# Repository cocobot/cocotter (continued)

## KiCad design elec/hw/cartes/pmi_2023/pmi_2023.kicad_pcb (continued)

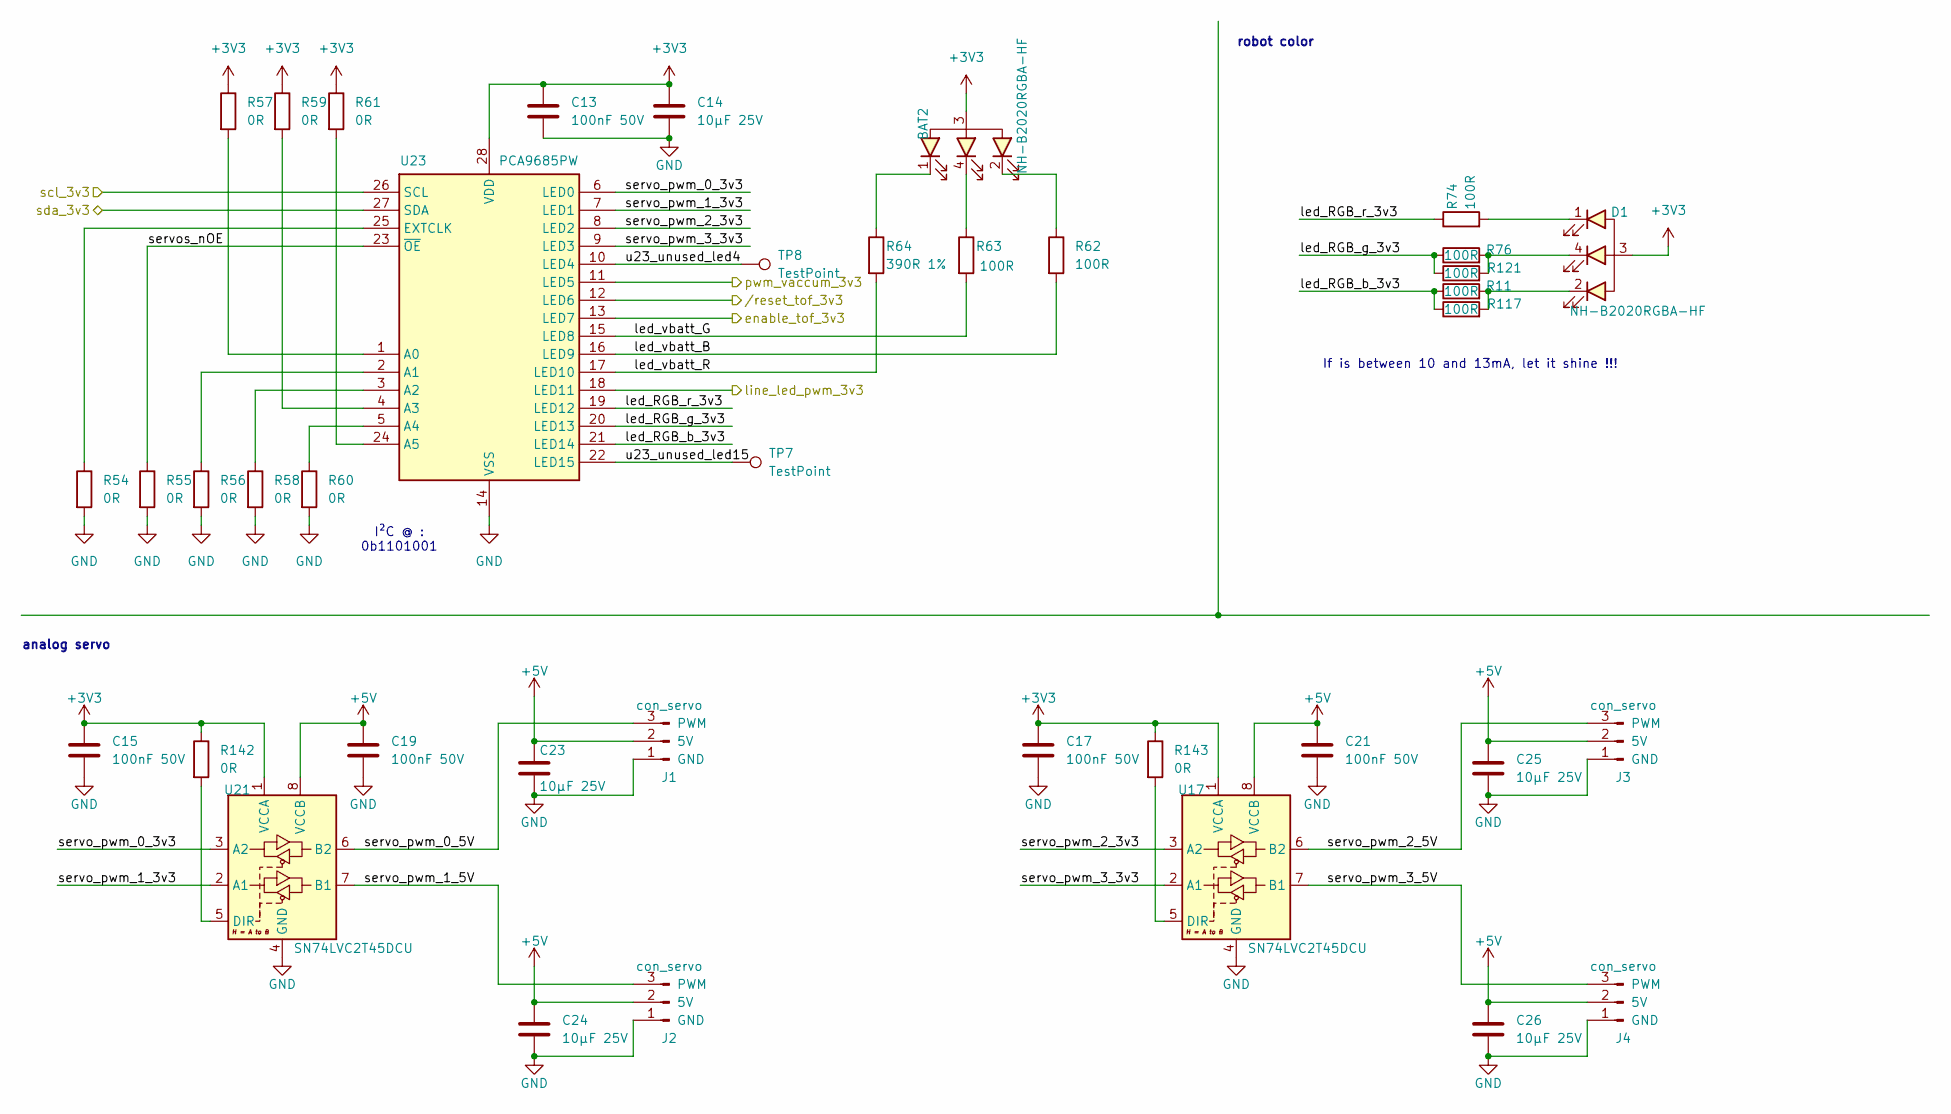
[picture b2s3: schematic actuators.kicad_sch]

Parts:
BAT2: NH-B2020RGBA-HF; JLCPCB Part # C2874116
C13, C15, C17, C19, C21: 100nF 50V; C_0603_1608Metric; JLCPCB Part # C14663
C14, C23, C24, C25, C26: 10µF 25V; C_0805_2012Metric; JLCPCB Part # C15850
D1: NH-B2020RGBA-HF; JLCPCB Part # C2874116
J1, J2, J3, J4: con_servo; ana_servo_5V; JLCPCB Part # C2932698
R11, R74, R76, R117, R121: 100R; r0603_reflow; JLCPCB Part # C22775
R54, R55, R56, R57, R58, R59, R60, R61, R142, R143: 0R; r0603_reflow; JLCPCB Part # C431718
R62, R63: 100R; r0603_reflow; mouser 603-RC0603FR-10100KL
R64: 390R 1%; r0603_reflow; mouser 603-RC0603FR-10100KL
TP7, TP8: TestPoint; testpoint-THT-0.5mm
U17, U21: SN74LVC2T45DCU; VSSOP-8-DCU
U23: PCA9685PW; TSSOP-28_4.4x9.7mm_P0.65mm; JLCPCB Part # C2678753

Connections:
+3V3: BAT2.3 (COM), C13.1, C14.1, C15.1, C17.1, D1.3 (COM), R57.1, R59.1, R61.1, R142.1, R143.1, U17.1 (VCCA), U21.1 (VCCA), U23.28 (VDD); also elsewhere on the board
+5V: C19.1, C21.1, C23.1, C24.1, C25.1, C26.1, J1.2 (5V), J2.2 (5V), J3.2 (5V), J4.2 (5V), U17.8 (VCCB), U21.8 (VCCB); also elsewhere on the board
/actuators/enable_tof_3v3: U23.13 (LED7); also elsewhere on the board
/actuators/led_RGB_b_3v3: R11.1, R117.1, U23.21 (LED14)
/actuators/led_RGB_g_3v3: R76.1, R121.1, U23.20 (LED13)
/actuators/led_RGB_r_3v3: R74.1, U23.19 (LED12)
/actuators/led_vbatt_B: R62.2, U23.16 (LED9)
/actuators/led_vbatt_G: R63.2, U23.15 (LED8)
/actuators/led_vbatt_R: R64.2, U23.17 (LED10)
/actuators/line_led_pwm_3v3: U23.18 (LED11); also elsewhere on the board
/actuators/scl_3v3: U23.26 (SCL); also elsewhere on the board
/actuators/sda_3v3: U23.27 (SDA); also elsewhere on the board
/actuators/servo_pwm_0_3v3: U21.3 (A2), U23.6 (LED0)
/actuators/servo_pwm_0_5V: J1.3 (PWM), U21.6 (B2)
/actuators/servo_pwm_1_3v3: U21.2 (A1), U23.7 (LED1)
/actuators/servo_pwm_1_5V: J2.3 (PWM), U21.7 (B1)
/actuators/servo_pwm_2_3v3: U17.3 (A2), U23.8 (LED2)
/actuators/servo_pwm_2_5V: J3.3 (PWM), U17.6 (B2)
/actuators/servo_pwm_3_3v3: U17.2 (A1), U23.9 (LED3)
/actuators/servo_pwm_3_5V: J4.3 (PWM), U17.7 (B1)
/actuators/servos_nOE: R55.1, U23.23 (~OE)
/actuators/u23_unused_led4: TP8.1, U23.10 (LED4)
/actuators/u23_unused_led15: TP7.1, U23.22 (LED15)
/actuators//reset_tof_3v3: U23.12 (LED6); also elsewhere on the board
/propulsion/pwm_vaccum_3v3: U23.11 (LED5); also elsewhere on the board
GND: C13.2, C14.2, C15.2, C17.2, C19.2, C21.2, C23.2, C24.2, C25.2, C26.2, J1.1 (GND), J2.1 (GND), J3.1 (GND), J4.1 (GND), R54.2, R55.2, R56.2, R58.2, R60.2, U17.4 (GND), U21.4 (GND), U23.14 (VSS); also elsewhere on the board
unnamed: BAT2.2 (C_BLUE), R62.1
unnamed: BAT2.4 (C_GREEN), R63.1
unnamed: BAT2.1 (C_RED), R64.1
unnamed: D1.2 (C_BLUE), R11.2, R117.2
unnamed: D1.4 (C_GREEN), R76.2, R121.2
unnamed: D1.1 (C_RED), R74.2
unnamed: R143.2, U17.5 (DIR)
unnamed: R142.2, U21.5 (DIR)
unnamed: R57.2, U23.1 (A0)
unnamed: R56.1, U23.2 (A1)
unnamed: R58.1, U23.3 (A2)
unnamed: R59.2, U23.4 (A3)
unnamed: R60.1, U23.5 (A4)
unnamed: R61.2, U23.24 (A5)
unnamed: R54.1, U23.25 (EXTCLK)

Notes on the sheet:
I²C @ : 0b1101001
If is between 10 and 13mA, let it shine !!!
robot color
analog servo

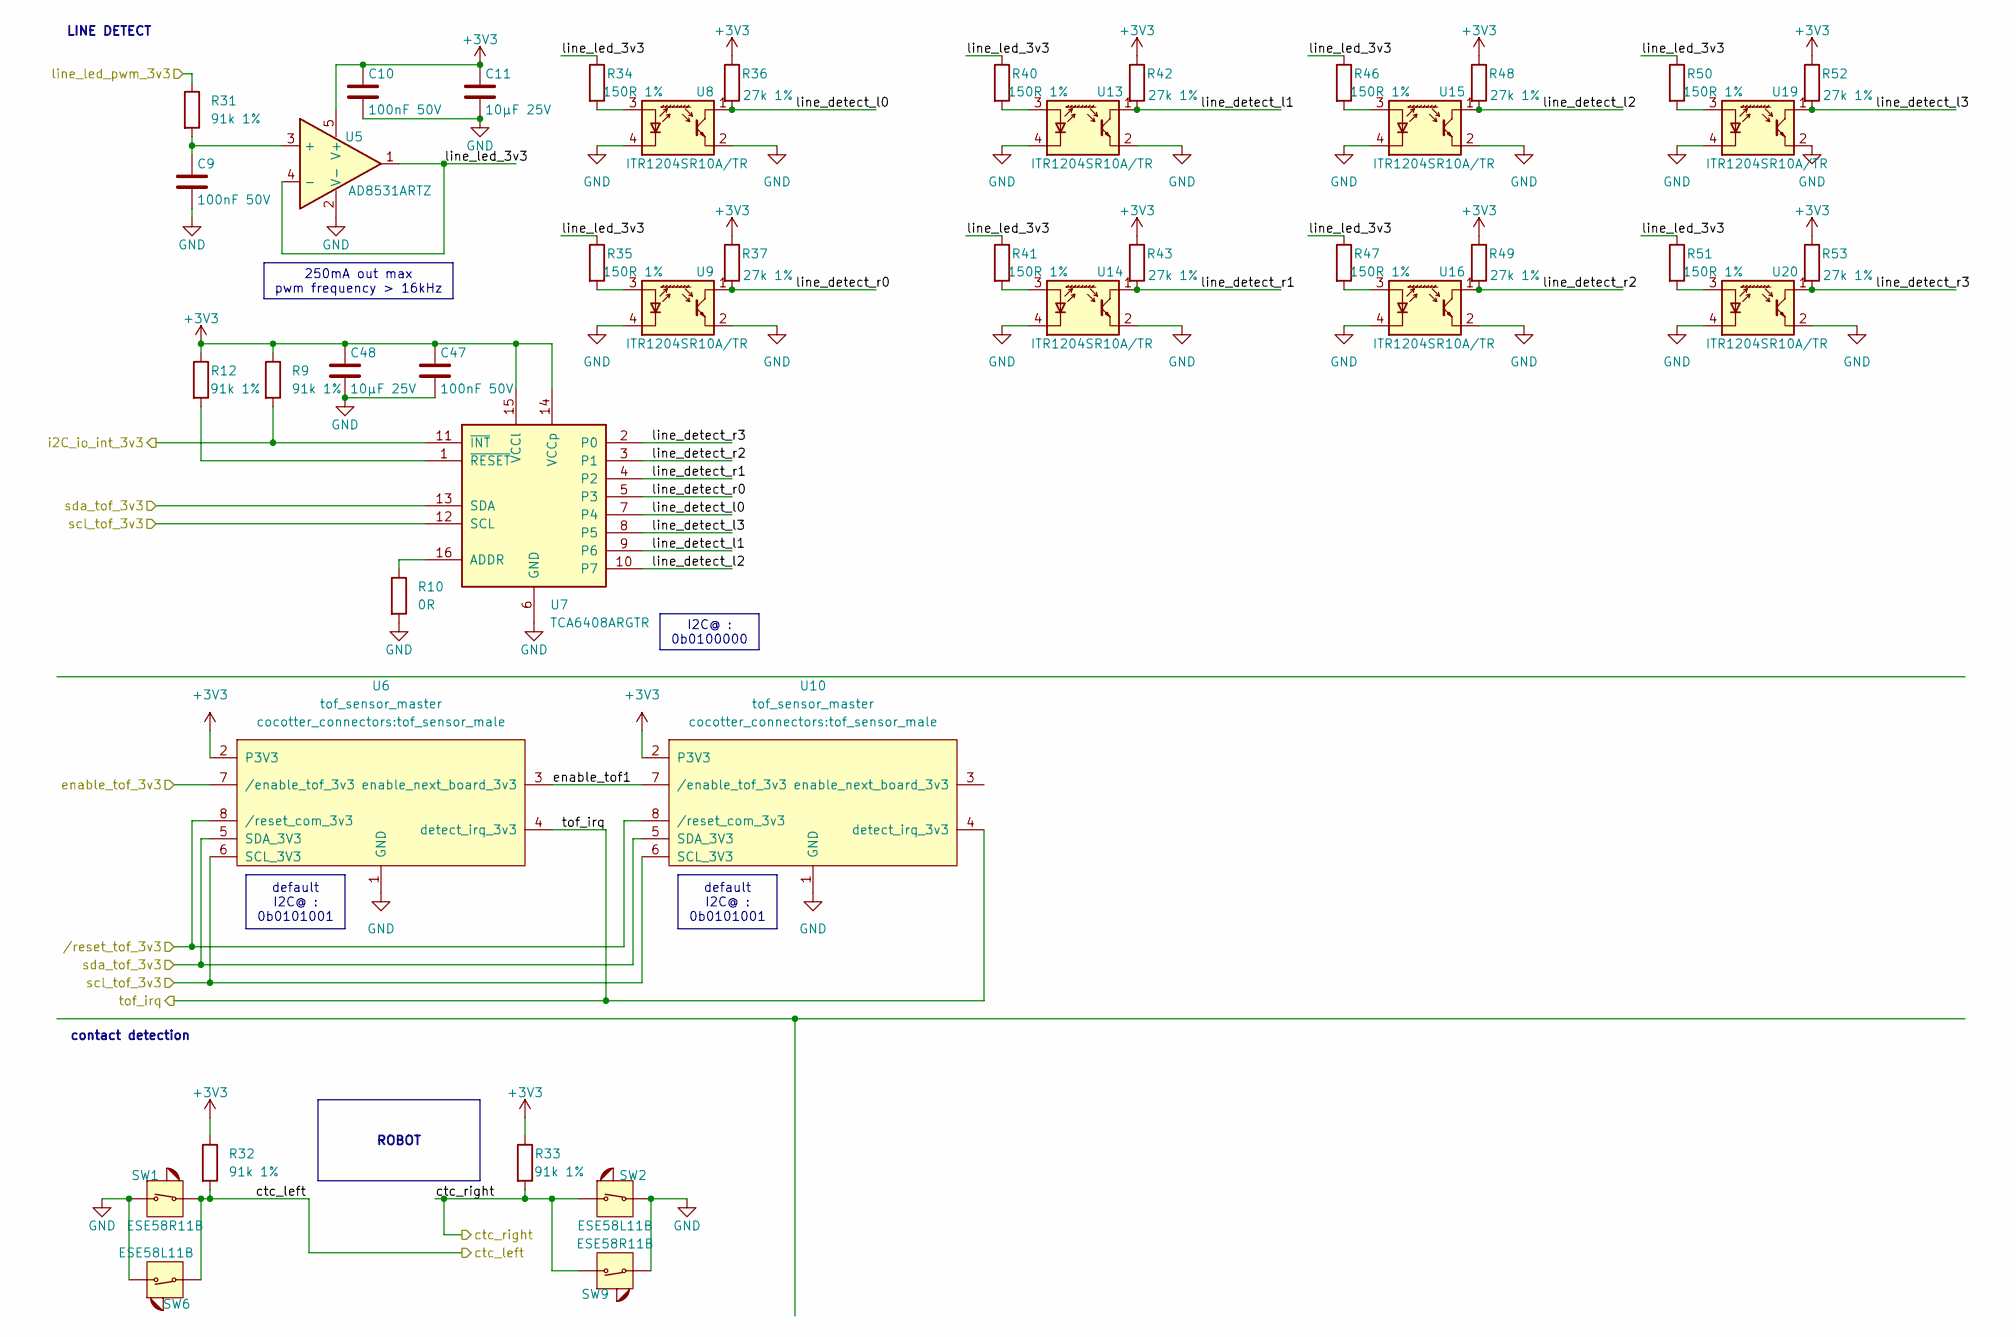
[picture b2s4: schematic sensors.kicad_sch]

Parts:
C9, C10, C47: 100nF 50V; C_0603_1608Metric; JLCPCB Part # C14663
C11, C48: 10µF 25V; C_0805_2012Metric; JLCPCB Part # C15850
R9, R12, R31, R32, R33: 91k 1%; r0603_reflow; JLCPCB Part # C23265
R10: 0R; r0603_reflow; JLCPCB Part # C431718
R34, R35, R40, R41, R46, R47, R50, R51: 150R 1%; r0805_reflow; JLCPCB Part # C17471
R36, R37, R42, R43, R48, R49, R52, R53: 27k 1%; r0603_reflow; JLCPCB Part # C22967
SW1, SW9: ESE58R11B; Mouser 667-ESE-22MH22
SW2, SW6: ESE58L11B; Mouser 667-ESE-22MH24
U5: AD8531ARTZ; SOT-23-5; MOUSER_REF 584-AD8531ARTZ-R7
U6, U10: tof_sensor_master; tof_sensor_male
U7: TCA6408ARGTR; VQFN-16-1EP_3x3mm_P0.5mm_EP1.1x1.1mm; mouser 595-TCA6408ARGTR
U8, U9, U13, U14, U15, U16, U19, U20: ITR1204SR10A/TR; ITR1204SR10A; JLCPCB Part # C2943466

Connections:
+3V3: C10.1, C11.1, C47.1, C48.1, R9.1, R12.1, R32.1, R33.1, R36.1, R37.1, R42.1, R43.1, R48.1, R49.1, R52.1, R53.1, U5.5 (V+), U6.2 (P3V3), U7.14 (VCCp), U7.15 (VCCl), U10.2 (P3V3); also elsewhere on the board
/actuators/enable_tof_3v3: U6.7 (/enable_tof_3v3); also elsewhere on the board
/actuators/line_led_pwm_3v3: R31.1; also elsewhere on the board
/actuators/scl_3v3: U6.6 (SCL_3V3), U7.12 (SCL), U10.6 (SCL_3V3); also elsewhere on the board
/actuators/sda_3v3: U6.5 (SDA_3V3), U7.13 (SDA), U10.5 (SDA_3V3); also elsewhere on the board
/actuators//reset_tof_3v3: U6.8 (/reset_com_3v3), U10.8 (/reset_com_3v3); also elsewhere on the board
/boards interface/i2C_io_int_3v3: R9.2, U7.11 (~INT); also elsewhere on the board
/sensors/ctc_left: R32.2, SW1.2, SW6.2; also elsewhere on the board
/sensors/ctc_right: R33.2, SW2.1, SW9.1; also elsewhere on the board
/sensors/enable_tof1: U6.3 (enable_next_board_3v3), U10.7 (/enable_tof_3v3)
/sensors/line_detect_l0: R36.2, U7.7 (P4), U8.1 (C)
/sensors/line_detect_l1: R42.2, U7.9 (P6), U13.1 (C)
/sensors/line_detect_l2: R48.2, U7.10 (P7), U15.1 (C)
/sensors/line_detect_l3: R52.2, U7.8 (P5), U19.1 (C)
/sensors/line_detect_r0: R37.2, U7.5 (P3), U9.1 (C)
/sensors/line_detect_r1: R43.2, U7.4 (P2), U14.1 (C)
/sensors/line_detect_r2: R49.2, U7.3 (P1), U16.1 (C)
/sensors/line_detect_r3: R53.2, U7.2 (P0), U20.1 (C)
/sensors/line_led_3v3: R34.1, R35.1, R40.1, R41.1, R46.1, R47.1, R50.1, R51.1, U5.1, U5.4 (-)
/sensors/tof_irq: U6.4 (detect_irq_3v3), U10.4 (detect_irq_3v3); also elsewhere on the board
GND: C9.2, C10.2, C11.2, C47.2, C48.2, R10.2, SW1.1, SW2.2, SW6.1, SW9.2, U5.2 (V-), U6.1 (GND), U7.6 (GND), U8.2 (E), U8.4 (K), U9.2 (E), U9.4 (K), U10.1 (GND), U13.2 (E), U13.4 (K), U14.2 (E), U14.4 (K), U15.2 (E), U15.4 (K), U16.2 (E), U16.4 (K), U19.2 (E), U19.4 (K), U20.2 (E), U20.4 (K); also elsewhere on the board
unnamed: C9.1, R31.2, U5.3 (+)
unnamed: R10.1, U7.16 (ADDR)
unnamed: R12.2, U7.1 (~RESET)
unnamed: R34.2, U8.3 (A)
unnamed: R35.2, U9.3 (A)
unnamed: R40.2, U13.3 (A)
unnamed: R41.2, U14.3 (A)
unnamed: R46.2, U15.3 (A)
unnamed: R47.2, U16.3 (A)
unnamed: R50.2, U19.3 (A)
unnamed: R51.2, U20.3 (A)

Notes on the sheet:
250mA out max pwm frequency > 16kHz
default I2C@ : 0b0101001
ROBOT
I2C@ : 0b0100000
contact detection
LINE DETECT

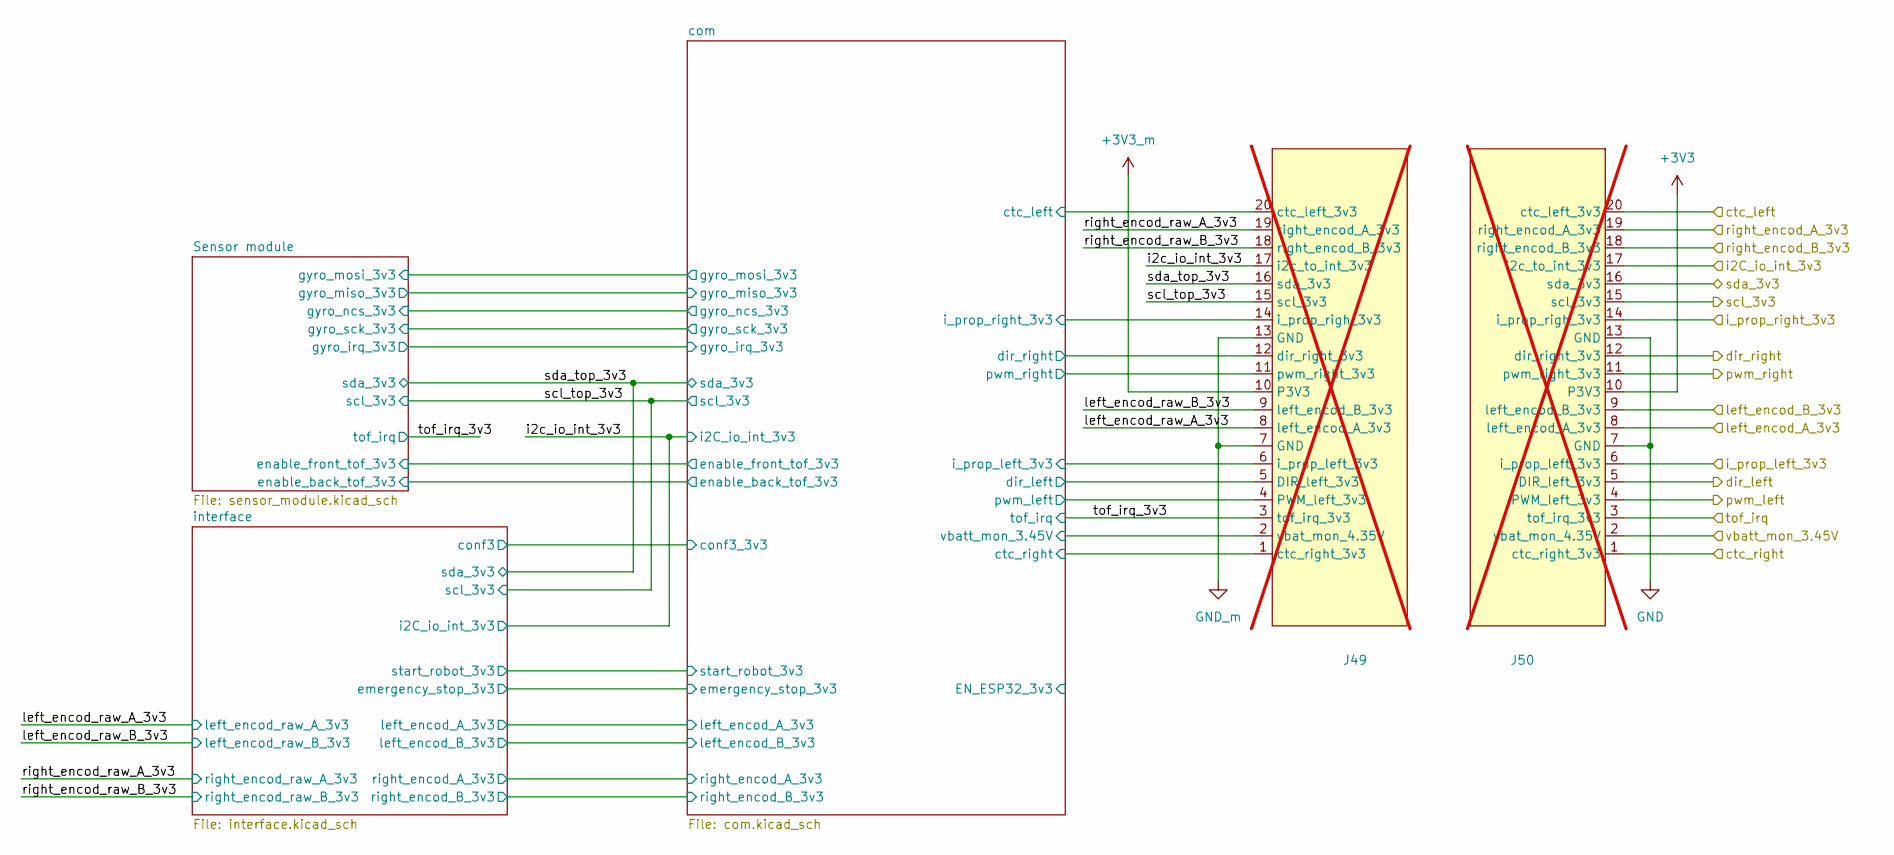
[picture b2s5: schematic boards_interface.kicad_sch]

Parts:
J49: pmi_2023_interconnection_top; not fitted
J50: pmi_2023_interconnection; not fitted

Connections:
+3V3: J50.10 (P3V3); also elsewhere on the board
+3V3_m: J49.10 (P3V3); also elsewhere on the board
/actuators/scl_3v3: J50.15 (scl_3v3); also elsewhere on the board
/actuators/sda_3v3: J50.16 (sda_3v3); also elsewhere on the board
/boards interface/com/ctc_left: J49.20 (ctc_left_3v3); also elsewhere on the board
/boards interface/com/ctc_right: J49.1 (ctc_right_3v3); also elsewhere on the board
/boards interface/com/dir_left: J49.5 (DIR_left_3v3); also elsewhere on the board
/boards interface/com/dir_right: J49.12 (dir_right_3v3); also elsewhere on the board
/boards interface/com/i_prop_left_3v3: J49.6 (i_prop_left_3v3); also elsewhere on the board
/boards interface/com/i_prop_right_3v3: J49.14 (i_prop_righ_3v3); also elsewhere on the board
/boards interface/com/pwm_left: J49.4 (PWM_left_3v3); also elsewhere on the board
/boards interface/com/pwm_right: J49.11 (pwm_right_3v3); also elsewhere on the board
/boards interface/com/vbatt_mon_3.45V: J49.2 (vbat_mon_4.35V); also elsewhere on the board
/boards interface/i2C_io_int_3v3: J50.17 (i2c_to_int_3v3); also elsewhere on the board
/boards interface/i2c_io_int_3v3: J49.17 (i2c_to_int_3v3); also elsewhere on the board
/boards interface/i_prop_left_3v3: J50.6 (i_prop_left_3v3); also elsewhere on the board
/boards interface/i_prop_right_3v3: J50.14 (i_prop_righ_3v3); also elsewhere on the board
/boards interface/left_encod_raw_A_3v3: J49.8 (left_encod_A_3v3); also elsewhere on the board
/boards interface/left_encod_raw_B_3v3: J49.9 (left_encod_B_3v3); also elsewhere on the board
/boards interface/right_encod_raw_A_3v3: J49.19 (right_encod_A_3v3); also elsewhere on the board
/boards interface/right_encod_raw_B_3v3: J49.18 (right_encod_B_3v3); also elsewhere on the board
/boards interface/scl_top_3v3: J49.15 (scl_3v3); also elsewhere on the board
/boards interface/sda_top_3v3: J49.16 (sda_3v3); also elsewhere on the board
/boards interface/tof_irq_3v3: J49.3 (tof_irq_3v3); also elsewhere on the board
/boards interface/vbatt_mon_3.45V: J50.2 (vbat_mon_4.35V); also elsewhere on the board
/propulsion/dir_left: J50.5 (DIR_left_3v3); also elsewhere on the board
/propulsion/dir_right: J50.12 (dir_right_3v3); also elsewhere on the board
/propulsion/left_encod_A_3v3: J50.8 (left_encod_A_3v3); also elsewhere on the board
/propulsion/left_encod_B_3v3: J50.9 (left_encod_B_3v3); also elsewhere on the board
/propulsion/pwm_left: J50.4 (PWM_left_3v3); also elsewhere on the board
/propulsion/pwm_right: J50.11 (pwm_right_3v3); also elsewhere on the board
/propulsion/right_encod_A_3v3: J50.19 (right_encod_A_3v3); also elsewhere on the board
/propulsion/right_encod_B_3v3: J50.18 (right_encod_B_3v3); also elsewhere on the board
/sensors/ctc_left: J50.20 (ctc_left_3v3); also elsewhere on the board
/sensors/ctc_right: J50.1 (ctc_right_3v3); also elsewhere on the board
/sensors/tof_irq: J50.3 (tof_irq_3v3); also elsewhere on the board
GND: J50.7 (GND), J50.13 (GND); also elsewhere on the board
GND_m: J49.7 (GND), J49.13 (GND); also elsewhere on the board

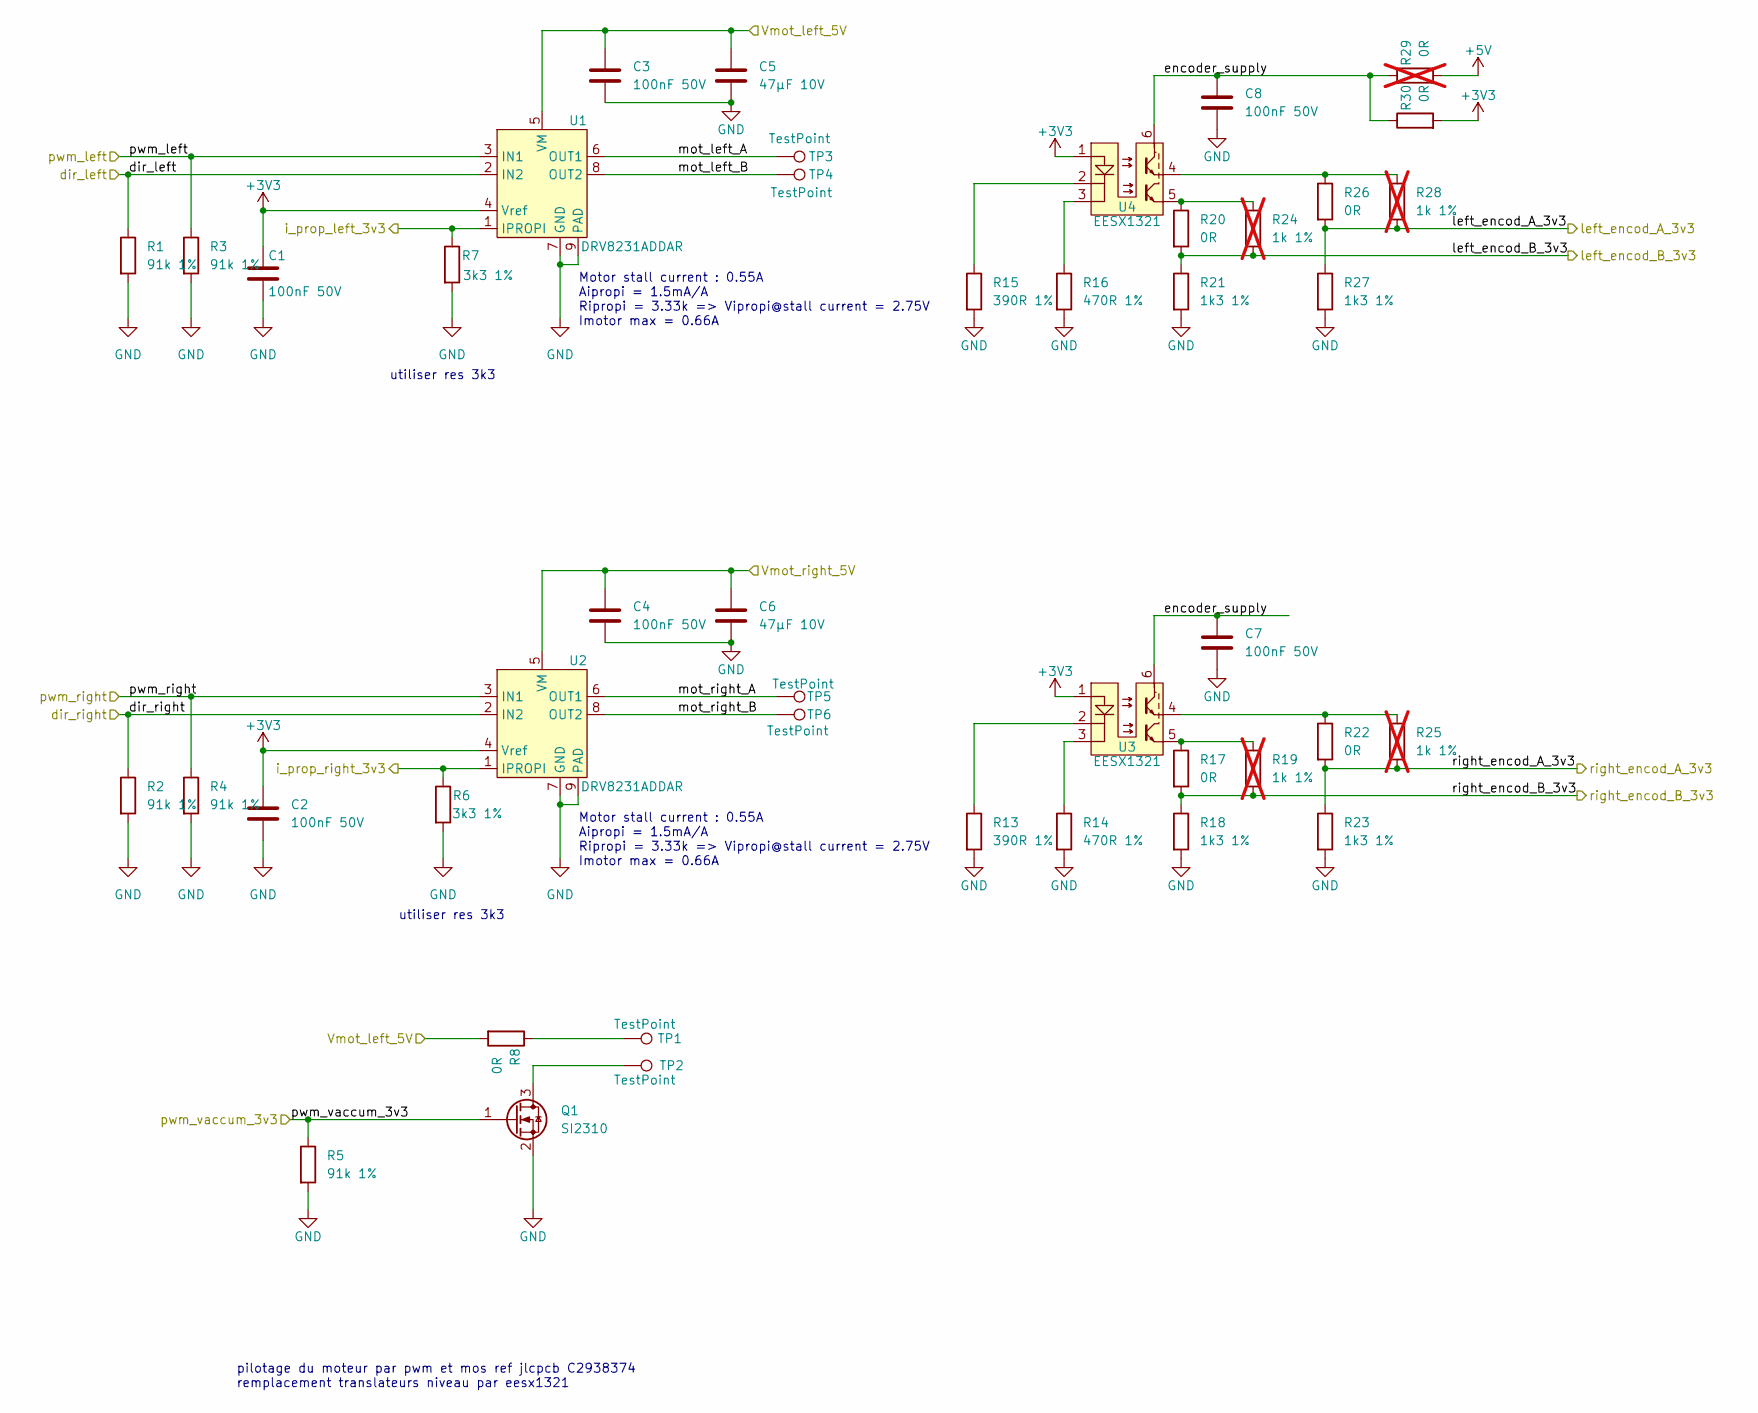
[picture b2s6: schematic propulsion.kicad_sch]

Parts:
C1, C2, C3, C4, C7, C8: 100nF 50V; C_0603_1608Metric; JLCPCB Part # C14663
C5, C6: 47µF 10V; C_1206_3216Metric; JLCPCB Part # C96123
Q1: SI2310; SOT-23-3; JLCPCB Part # C2938374
R1, R2, R3, R4, R5: 91k 1%; r0603_reflow; JLCPCB Part # C23265
R6, R7: 3k3 1%; r0603_reflow; JLCPCB Part # C22978
R8, R17, R20, R22, R26, R30: 0R; r0603_reflow; JLCPCB Part # C431718
R13, R15: 390R 1%; r0603_reflow; JLCPCB Part # C23151
R14, R16: 470R 1%; r0603_reflow; JLCPCB Part # C23179
R18, R21, R23, R27: 1k3 1%; r0603_reflow; JLCPCB Part # C22767
R19, R24, R25, R28: 1k 1%; r0603_reflow; mouser 603-RC0603FR-10100KL; not fitted
R29: 0R; r0603_reflow; JLCPCB Part # C431718; not fitted
TP1, TP2, TP3, TP4, TP5, TP6: TestPoint; testpoint-THT-0.5mm
U1, U2: DRV8231ADDAR; DDA0008B; JLCPCB Part # C5218849
U3, U4: EESX1321

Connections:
+3V3: C1.1, C2.1, R30.2, U1.4 (Vref), U2.4 (Vref), U3.1 (A), U4.1 (A); also elsewhere on the board
+5V: R29.2; also elsewhere on the board
/boards interface/i_prop_left_3v3: R7.1, U1.1 (IPROPI); also elsewhere on the board
/boards interface/i_prop_right_3v3: R6.1, U2.1 (IPROPI); also elsewhere on the board
/power_supply/Vmot_left_5V: C3.1, C5.1, R8.2, U1.5 (VM); also elsewhere on the board
/power_supply/Vmot_right_5V: C4.1, C6.1, U2.5 (VM); also elsewhere on the board
/propulsion/dir_left: R1.1, U1.2 (IN2); also elsewhere on the board
/propulsion/dir_right: R2.1, U2.2 (IN2); also elsewhere on the board
/propulsion/encoder_supply: C7.1, C8.1, R29.1, R30.1, U3.6 (C), U4.6 (C)
/propulsion/left_encod_A_3v3: R26.2, R27.1, R28.2; also elsewhere on the board
/propulsion/left_encod_B_3v3: R20.2, R21.1, R24.2; also elsewhere on the board
/propulsion/mot_left_A: TP3.1, U1.6 (OUT1)
/propulsion/mot_left_B: TP4.1, U1.8 (OUT2)
/propulsion/mot_right_A: TP5.1, U2.6 (OUT1)
/propulsion/mot_right_B: TP6.1, U2.8 (OUT2)
/propulsion/pwm_left: R3.1, U1.3 (IN1); also elsewhere on the board
/propulsion/pwm_right: R4.1, U2.3 (IN1); also elsewhere on the board
/propulsion/pwm_vaccum_3v3: Q1.1 (G), R5.1; also elsewhere on the board
/propulsion/right_encod_A_3v3: R22.2, R23.1, R25.2; also elsewhere on the board
/propulsion/right_encod_B_3v3: R17.2, R18.1, R19.2; also elsewhere on the board
GND: C1.2, C2.2, C3.2, C4.2, C5.2, C6.2, C7.2, C8.2, Q1.2 (S), R1.2, R2.2, R3.2, R4.2, R5.2, R6.2, R7.2, R13.2, R14.2, R15.2, R16.2, R18.2, R21.2, R23.2, R27.2, U1.7 (GND), U1.9 (PAD), U2.7 (GND), U2.9 (PAD); also elsewhere on the board
unnamed: Q1.3 (D), TP2.1
unnamed: R8.1, TP1.1
unnamed: R13.1, U3.2 (C1)
unnamed: R14.1, U3.3 (C2)
unnamed: R22.1, R25.1, U3.4 (E1)
unnamed: R17.1, R19.1, U3.5 (E2)
unnamed: R15.1, U4.2 (C1)
unnamed: R16.1, U4.3 (C2)
unnamed: R26.1, R28.1, U4.4 (E1)
unnamed: R20.1, R24.1, U4.5 (E2)

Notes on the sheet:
utiliser res 3k3
Motor stall current : 0.55A Aipropi = 1.5mA/A Ripropi = 3.33k => Vipropi@stall current = 2.75V Imotor max = 0.66A
pilotage du moteur par pwm et mos ref jlcpcb C2938374 remplacement translateurs niveau par eesx1321

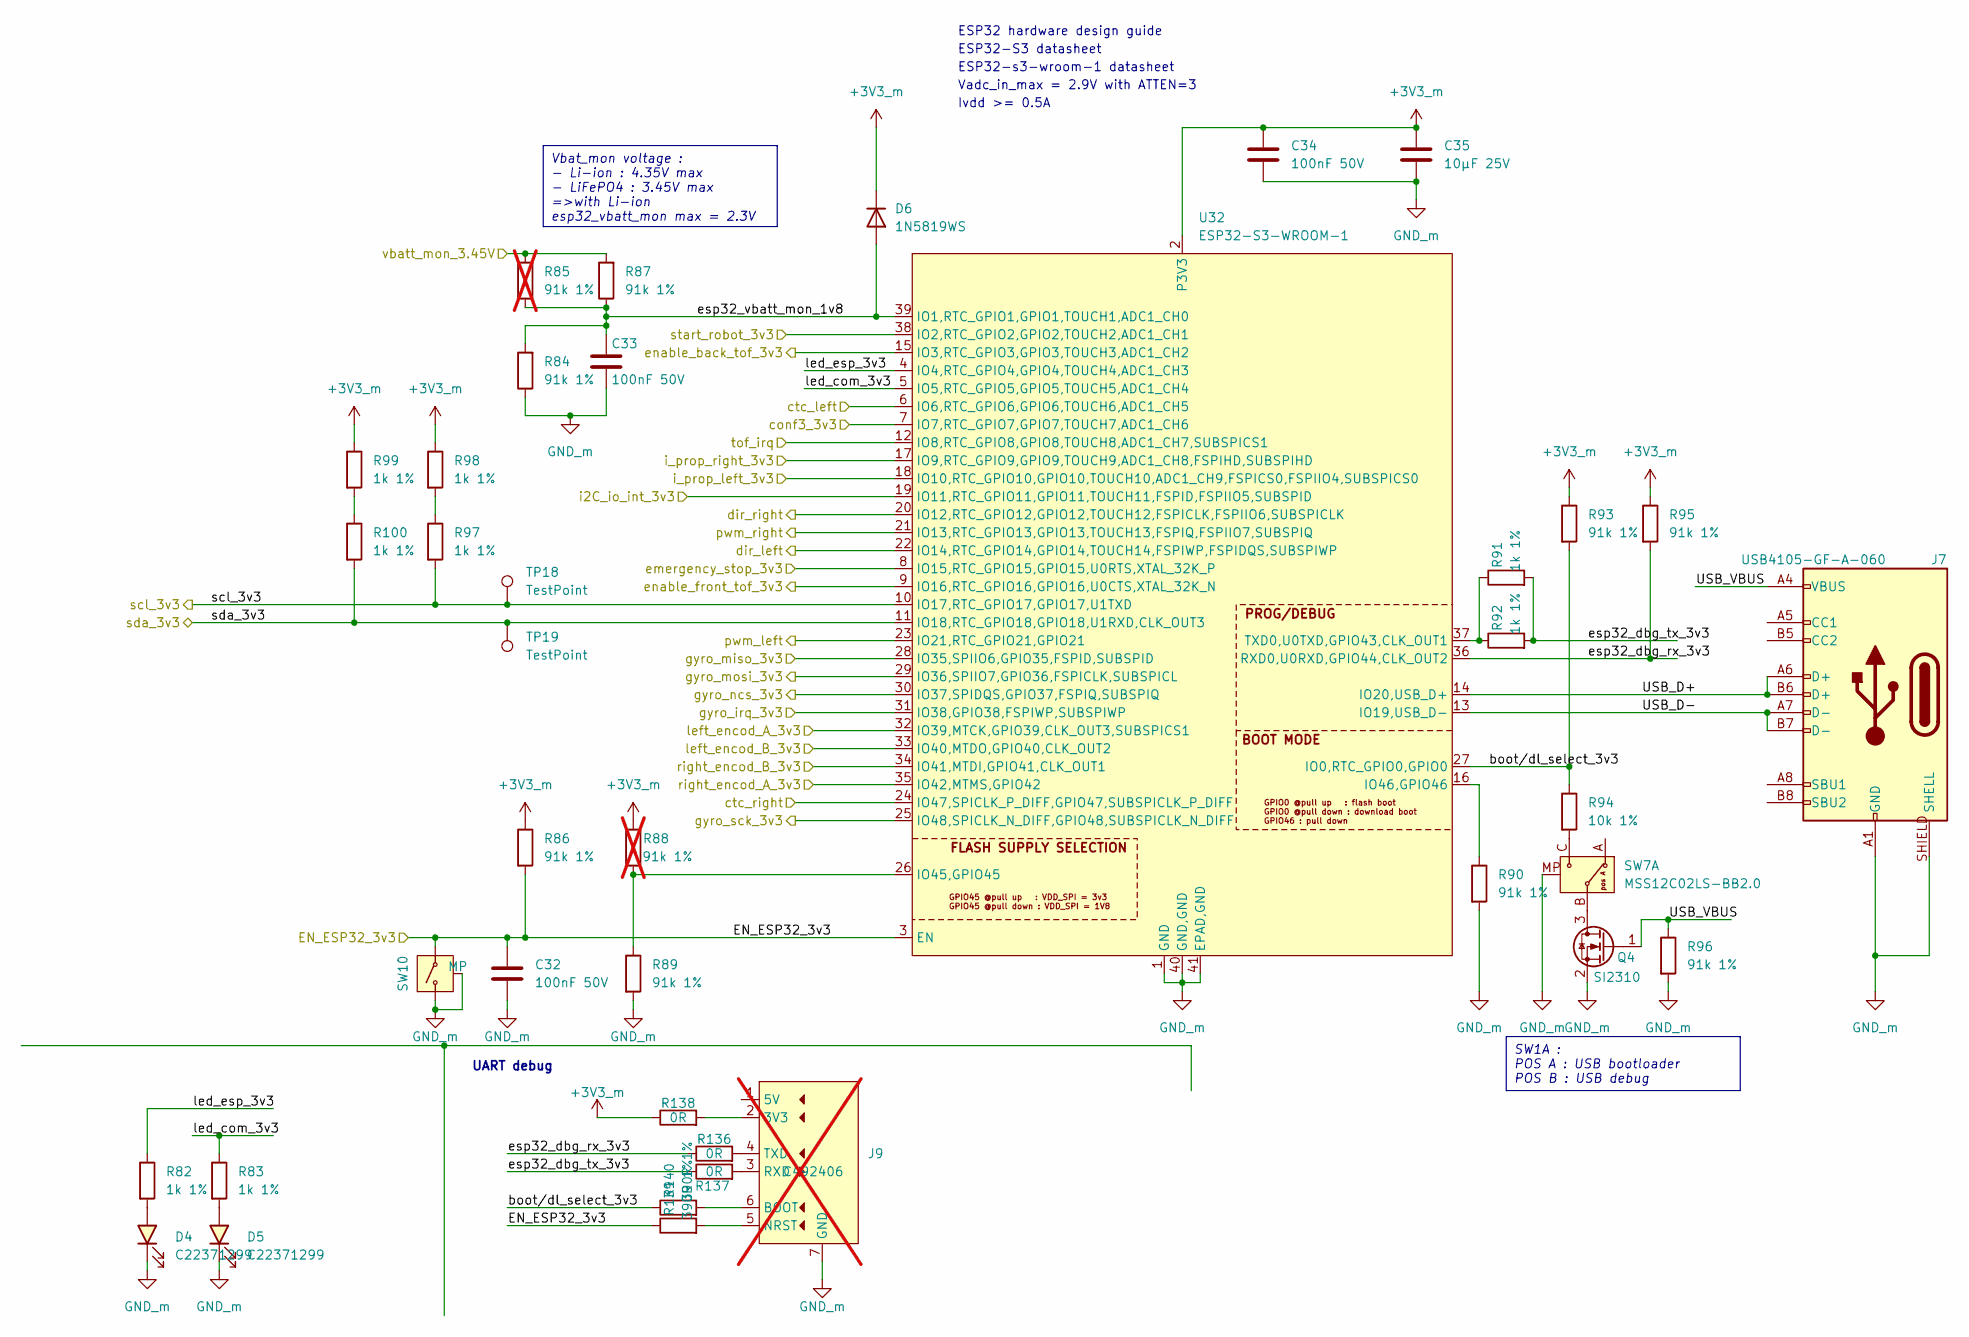
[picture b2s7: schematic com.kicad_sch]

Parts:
C32, C33, C34: 100nF 50V; C_0603_1608Metric; JLCPCB Part # C14663
C35: 10µF 25V; C_0805_2012Metric; JLCPCB Part # C15850
D4, D5: green, 0603; LED_0603_1608Metric; DIGIKEY_REF 3147-B19Y1UYG-20C000313U1930CT-ND
D6: 1N5819WS; D_SOD-323F; JLCPCB C191023
J7: USB4105-GF-A-060; USB4105; DIGIKEY_REF 2073-USB4105-GF-A-060TR-ND
J9: eps32_uart_programmer; JLCPCB Part # C492406; not fitted
Q4: SI2310; SOT-23-3; JLCPCB Part # C2938374
R82, R83, R91, R92, R97, R98, R99, R100: 1k 1%; r0603_reflow; mouser 603-RC0603FR-10100KL
R84, R86, R89, R90, R93, R95, R96: 91k 1%; r0603_reflow; JLCPCB Part # C23265
R85, R88: 91k 1%; r0603_reflow; JLCPCB Part # C23265; not fitted
R87: 91k 1%; r0603_reflow; mouser 603-RC0603FR-10100KL
R94: 10k 1%; r0603_reflow; mouser 603-RC0603FR-10100KL
R136, R137, R138: 0R; r0603_reflow; JLCPCB Part # C431718
R139, R140: 390R 1%; r0603_reflow; JLCPCB Part # C23151
SW7: MSS12C02LS-BB2.0; JLCPCB Part # C3008585
SW10: TSB001A3526A02; JLCPCB Part # C2888889
TP18, TP19: TestPoint; testpoint-THT-0.5mm
U32: ESP32-S3-WROOM-1; JLCPCB Part # C3013944

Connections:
+3V3_m: C34.1, C35.1, D6.1 (K), R86.1, R88.1, R93.1, R95.1, R98.1, R99.1, R138.1, U32.2 (P3V3); also elsewhere on the board
/boards interface/Sensor module/enable_back_tof_3v3: U32.15 (IO3,RTC_GPIO3,GPIO3,TOUCH3,ADC1_CH2); also elsewhere on the board
/boards interface/Sensor module/enable_front_tof_3v3: U32.9 (IO16,RTC_GPIO16,GPIO16,U0CTS,XTAL_32K_N); also elsewhere on the board
/boards interface/Sensor module/gyro_irq_3v3: U32.31 (IO38,GPIO38,FSPIWP,SUBSPIWP); also elsewhere on the board
/boards interface/Sensor module/gyro_miso_3v3: U32.28 (IO35,SPIIO6,GPIO35,FSPID,SUBSPID); also elsewhere on the board
/boards interface/Sensor module/gyro_mosi_3v3: U32.29 (IO36,SPIIO7,GPIO36,FSPICLK,SUBSPICL); also elsewhere on the board
/boards interface/Sensor module/gyro_ncs_3v3: U32.30 (IO37,SPIDQS,GPIO37,FSPIQ,SUBSPIQ); also elsewhere on the board
/boards interface/Sensor module/gyro_sck_3v3: U32.25 (IO48,SPICLK_N_DIFF,GPIO48,SUBSPICLK_N_D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); also elsewhere on the board
/boards interface/com/EN_ESP32_3v3: C32.1, R86.2, R139.1, SW10.2, U32.3 (EN)
/boards interface/com/USB_D+: J7.A6 (D+), J7.B6 (D+), U32.14 (IO20,USB_D+)
/boards interface/com/USB_D-: J7.A7 (D-), J7.B7 (D-), U32.13 (IO19,USB_D-)
/boards interface/com/USB_VBUS: J7.A4 (VBUS), J7.A9 (VBUS), J7.B4 (VBUS), J7.B9 (VBUS), Q4.1 (G), R96.1
/boards interface/com/boot/dl_select_3v3: R93.2, R94.1, R140.1, U32.27 (IO0,RTC_GPIO0,GPIO0)
/boards interface/com/ctc_left: U32.6 (IO6,RTC_GPIO6,GPIO6,TOUCH6,ADC1_CH5); also elsewhere on the board
/boards interface/com/ctc_right: U32.24 (IO47,SPICLK_P_DIFF,GPIO47,SUBSPICLK_P_D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); also elsewhere on the board
/boards interface/com/dir_left: U32.22 (IO14,RTC_GPIO14,GPIO14,TOUCH14,FSPIWP,F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); also elsewhere on the board
/boards interface/com/dir_right: U32.20 (IO12,RTC_GPIO12,GPIO12,TOUCH12,FSPICLK,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); also elsewhere on the board
/boards interface/com/emergency_stop_3v3: U32.8 (IO15,RTC_GPIO15,GPIO15,U0RTS,XTAL_32K_P); also elsewhere on the board
/boards interface/com/esp32_dbg_rx_3v3: R95.2, R136.1, U32.36 (RXD0,U0RXD,GPIO44,CLK_OUT2)
/boards interface/com/esp32_dbg_tx_3v3: R91.2, R92.2, R137.1
/boards interface/com/esp32_vbatt_mon_1v8: C33.1, D6.2 (A), R84.2, R85.1, R87.1, U32.39 (IO1,RTC_GPIO1,GPIO1,TOUCH1,ADC1_CH0)
/boards interface/com/i_prop_left_3v3: U32.18 (IO10,RTC_GPIO10,GPIO10,TOUCH10,ADC1_CH9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); also elsewhere on the board
/boards interface/com/i_prop_right_3v3: U32.17 (IO9,RTC_GPIO9,GPIO9,TOUCH9,ADC1_CH8,FSP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); also elsewhere on the board
/boards interface/com/led_com_3v3: R83.1, U32.5 (IO5,RTC_GPIO5,GPIO5,TOUCH5,ADC1_CH4)
/boards interface/com/led_esp_3v3: R82.1, U32.4 (IO4,RTC_GPIO4,GPIO4,TOUCH4,ADC1_CH3)
/boards interface/com/left_encod_A_3v3: U32.32 (IO39,MTCK,GPIO39,CLK_OUT3,SUBSPICS1); also elsewhere on the board
/boards interface/com/left_encod_B_3v3: U32.33 (IO40,MTDO,GPIO40,CLK_OUT2); also elsewhere on the board
/boards interface/com/pwm_left: U32.23 (IO21,RTC_GPIO21,GPIO21); also elsewhere on the board
/boards interface/com/pwm_right: U32.21 (IO13,RTC_GPIO13,GPIO13,TOUCH13,FSPIQ,FS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); also elsewhere on the board
/boards interface/com/right_encod_A_3v3: U32.35 (IO42,MTMS,GPIO42); also elsewhere on the board
/boards interface/com/right_encod_B_3v3: U32.34 (IO41,MTDI,GPIO41,CLK_OUT1); also elsewhere on the board
/boards interface/com/start_robot_3v3: U32.38 (IO2,RTC_GPIO2,GPIO2,TOUCH2,ADC1_CH1); also elsewhere on the board
/boards interface/com/vbatt_mon_3.45V: R85.2, R87.2; also elsewhere on the board
/boards interface/i2c_io_int_3v3: U32.19 (IO11,RTC_GPIO11,GPIO11,TOUCH11,FSPID,FS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); also elsewhere on the board
/boards interface/interface/conf3: U32.7 (IO7,RTC_GPIO7,GPIO7,TOUCH7,ADC1_CH6); also elsewhere on the board
/boards interface/scl_top_3v3: R97.2, TP18.1, U32.10 (IO17,RTC_GPIO17,GPIO17,U1TXD); also elsewhere on the board
/boards interface/sda_top_3v3: R100.2, TP19.1, U32.11 (IO18,RTC_GPIO18,GPIO18,U1RXD,CLK_OUT3); also elsewhere on the board
/boards interface/tof_irq_3v3: U32.12 (IO8,RTC_GPIO8,GPIO8,TOUCH8,ADC1_CH7,SUB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); also elsewhere on the board
GND_m: C32.2, C33.2, C34.2, C35.2, D4.C, D5.C, J7.A1 (GND), J7.A12 (GND), J7.B1 (GND), J7.B12 (GND), J7.SHIELD (SHELL), J9.7 (GND), Q4.2 (S), R84.1, R89.2, R90.2, R96.2, SW7.MP, SW10.1, SW10.MP, U32.1 (GND), U32.40 (GND,GND), U32.41 (EPAD,GND); also elsewhere on the board
unnamed: D4.A, R82.2
unnamed: D5.A, R83.2
unnamed: J9.2 (3V3), R138.2
unnamed: J9.6 (BOOT), R140.2
unnamed: J9.5 (NRST), R139.2
unnamed: J9.3 (RXD), R137.2
unnamed: J9.4 (TXD), R136.2
unnamed: Q4.3 (D), SW7.B
unnamed: R94.2, SW7.C
unnamed: R97.1, R98.2
unnamed: R99.2, R100.1
unnamed: R88.2, R89.1, U32.26 (IO45,GPIO45)
unnamed: R90.1, U32.16 (IO46,GPIO46)
unnamed: R91.1, R92.1, U32.37 (TXD0,U0TXD,GPIO43,CLK_OUT1)

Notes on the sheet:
Vbat_mon voltage : - Li-ion : 4.35V max - LiFePO4 : 3.45V max =>with Li-ion esp32_vbatt_mon max = 2.3V
SW1A : POS A : USB bootloader POS B : USB debug
ESP32-s3-wroom-1 datasheet
ESP32-S3 datasheet
ESP32 hardware design guide
UART debug
Ivdd >= 0.5A
Vadc_in_max = 2.9V with ATTEN=3
